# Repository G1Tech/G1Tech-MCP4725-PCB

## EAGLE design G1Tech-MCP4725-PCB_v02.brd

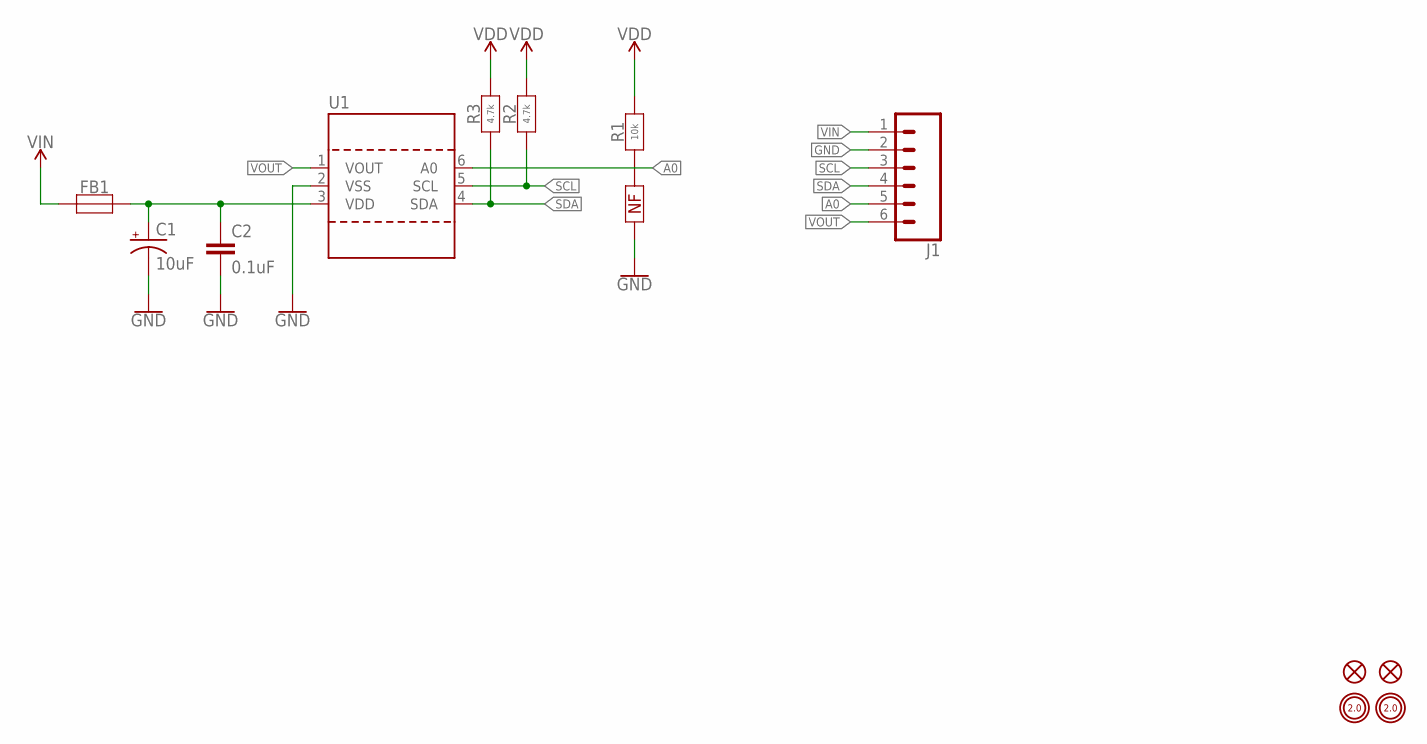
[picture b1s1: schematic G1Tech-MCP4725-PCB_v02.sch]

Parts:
C1: 10uF; TYPE-A
C2: 0.1uF; C0603
FB1: FERRITE-BEAD-0603; FB-0603
FD1, FD2: FIDUCIAL-1X2
H1, H2: MOUNTINGHOLE-PLATED-2.0
J1: CONN-1X6; 1X06_NO_SILK
R1: 10k; YAGEO-JP0603
R2, R3: 4.7k; YAGEO-R0603
U1: MCP4725; SOT23-6

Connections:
A0: J1.5, R1.2, U1.6 (A0)
GND: C1.C, C2.2, J1.2, R1.3, U1.2 (VSS)
SCL: J1.3, R2.1, U1.5 (SCL)
SDA: J1.4, R3.1, U1.4 (SDA)
VDD: C1.A, C2.1, FB1.2, R1.1, R2.2, R3.2, U1.3 (VDD)
VIN: FB1.1, J1.1
VOUT: J1.6, U1.1 (VOUT)

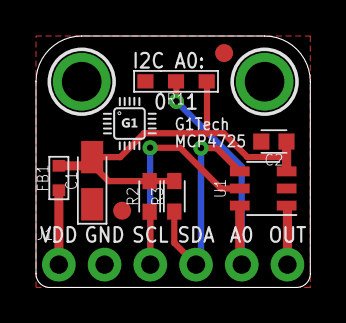
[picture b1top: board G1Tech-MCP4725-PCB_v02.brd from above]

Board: 2 copper layers, 15.2 x 14.0 mm, 14 parts (1 on the bottom side), 7 nets.

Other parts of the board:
U$1, U$2: LOGO-G1TECH-3MM
